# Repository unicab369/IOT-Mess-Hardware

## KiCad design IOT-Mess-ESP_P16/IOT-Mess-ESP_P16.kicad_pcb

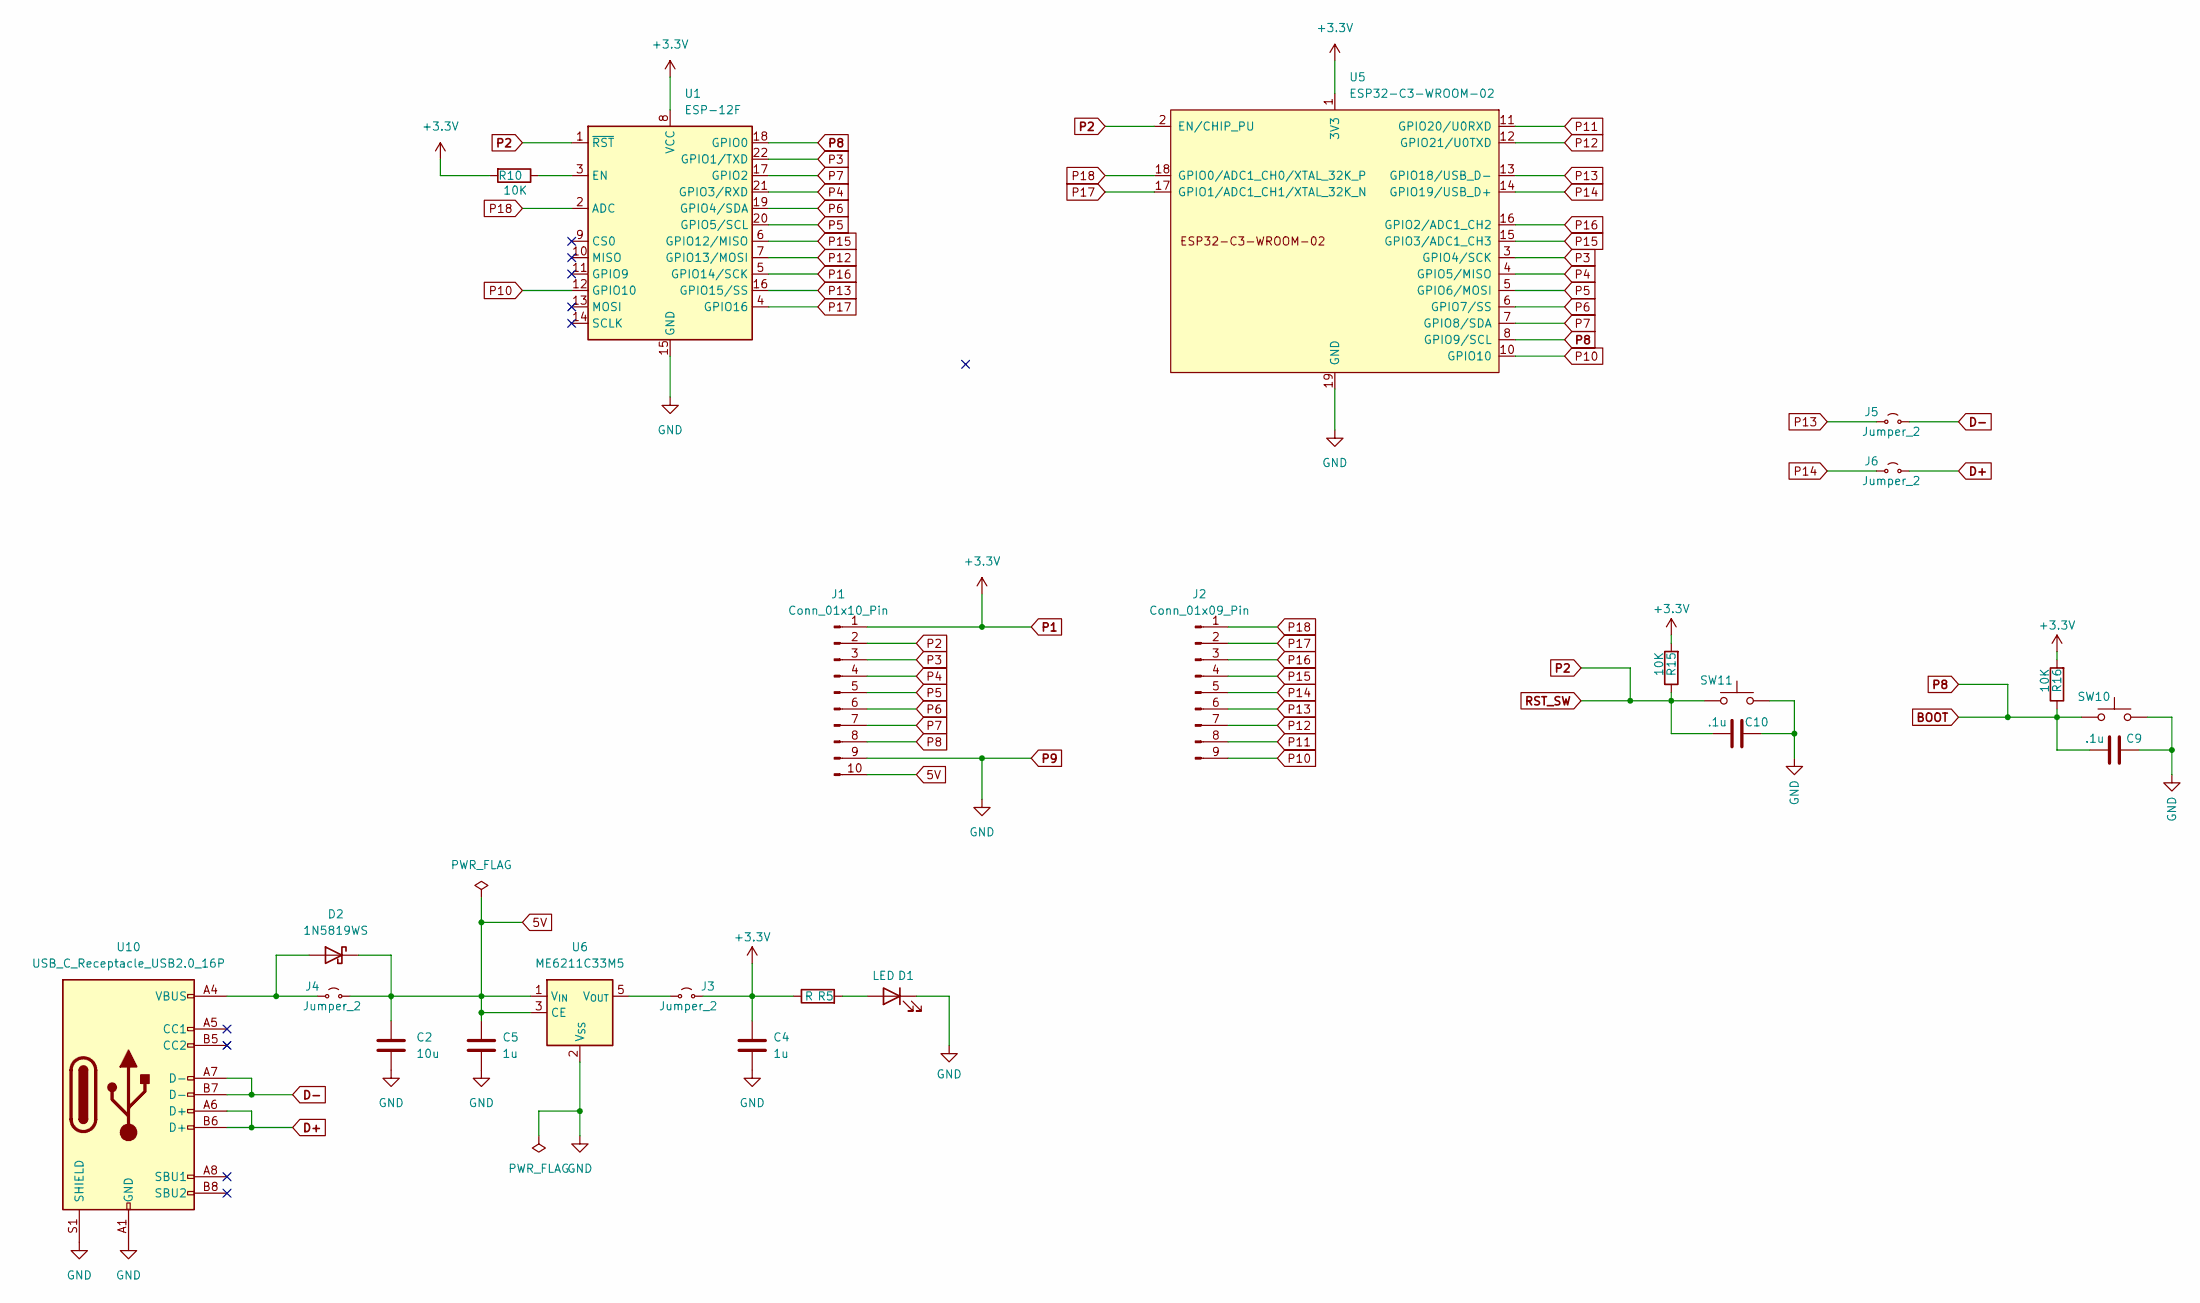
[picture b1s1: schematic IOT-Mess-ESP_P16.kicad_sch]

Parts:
C2: 10u; C_0603_1608Metric
C4, C5: 1u; C_0603_1608Metric
C9, C10: .1u; C_0603_1608Metric
D1: LED; LED_0603_1608Metric
D2: 1N5819WS; D_SOD-323
J1: Conn_01x10_Pin; PinHeader_1x10_P2.54mm_Vertical
J2: Conn_01x09_Pin; PinHeader_1x09_P2.54mm_Vertical
J3, J4, J5, J6: Jumper_2; Jumpper-triangle
R5: R; R_0603_1608Metric
R10, R15, R16: 10K; R_0603_1608Metric
SW10, SW11: SW_Push; SW_SPST_PTS810
U1: ESP-12F; ESP-12E
U5: ESP32-C3-WROOM-02
U6: ME6211C33M5; SOT-23-5
U10: USB_C_Receptacle_USB2.0_16P; USB_C_Receptacle_HRO_TYPE-C-31-M-12

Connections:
5V: C2.1, C5.1, D2.1 (K), J1.10, J4.2 (B), U6.1 (V_{IN}), U6.3 (CE)
BOOT: C9.1, J1.8, R16.1, SW10.1, U1.18 (GPIO0), U5.8 (GPIO9/SCL)
D+: J6.2 (B), U10.A6 (D+), U10.B6 (D+)
D-: J5.2 (B), U10.A7 (D-), U10.B7 (D-)
unnamed: D1.2 (A), R5.2
unnamed: D2.2 (A), J4.1 (A), U10.A4 (VBUS), U10.A9 (VBUS), U10.B4 (VBUS), U10.B9 (VBUS)
unnamed: J3.2 (B), U6.5 (V_{OUT})
unnamed: R10.1, U1.3 (EN)
P1: C4.1, J1.1, J3.1 (A), R5.1, R10.2, R15.2, R16.2, U1.8 (VCC), U5.1 (3V3)
P2: C10.1, J1.2, R15.1, SW11.1, U1.1 (~RST), U5.2 (EN/CHIP_PU)
P3: J1.3, U1.22 (GPIO1/TXD), U5.3 (GPIO4/SCK)
P4: J1.4, U1.21 (GPIO3/RXD), U5.4 (GPIO5/MISO)
P5: J1.5, U1.20 (GPIO5/SCL), U5.5 (GPIO6/MOSI)
P6: J1.6, U1.19 (GPIO4/SDA), U5.6 (GPIO7/SS)
P7: J1.7, U1.17 (GPIO2), U5.7 (GPIO8/SDA)
P9: C2.2, C4.2, C5.2, C9.2, C10.2, D1.1 (K), J1.9, SW10.2, SW11.2, U1.15 (GND), U5.9 (GND), U5.19 (GND), U6.2 (V_{SS}), U10.A1 (GND), U10.A12 (GND), U10.B1 (GND), U10.B12 (GND), U10.S1 (SHIELD)
P10: J2.9, U1.12 (GPIO10), U5.10 (GPIO10)
P11: J2.8, U5.11 (GPIO20/U0RXD)
P12: J2.7, U1.7 (GPIO13/MOSI), U5.12 (GPIO21/U0TXD)
P13: J2.6, J5.1 (A), U1.16 (GPIO15/SS), U5.13 (GPIO18/USB_D-)
P14: J2.5, J6.1 (A), U5.14 (GPIO19/USB_D+)
P15: J2.4, U1.6 (GPIO12/MISO), U5.15 (GPIO3/ADC1_CH3)
P16: J2.3, U1.5 (GPIO14/SCK), U5.16 (GPIO2/ADC1_CH2)
P17: J2.2, U1.4 (GPIO16), U5.17 (GPIO1/ADC1_CH1/XTAL_32K_N)
P18: J2.1, U1.2 (ADC), U5.18 (GPIO0/ADC1_CH0/XTAL_32K_P)

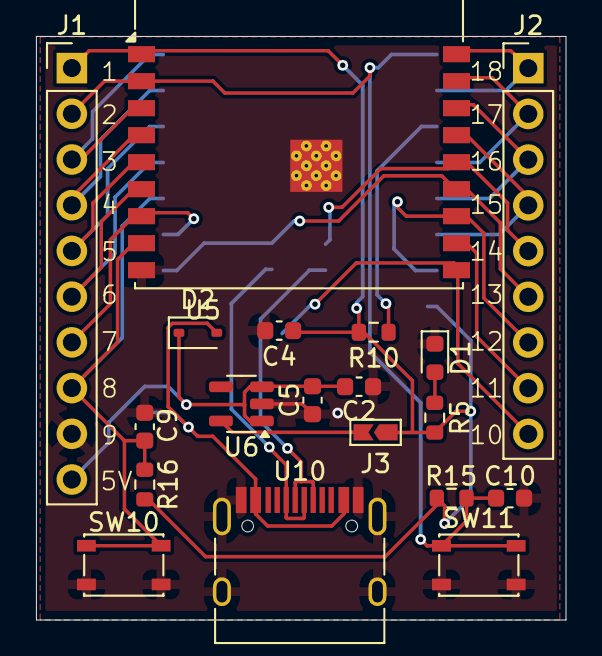
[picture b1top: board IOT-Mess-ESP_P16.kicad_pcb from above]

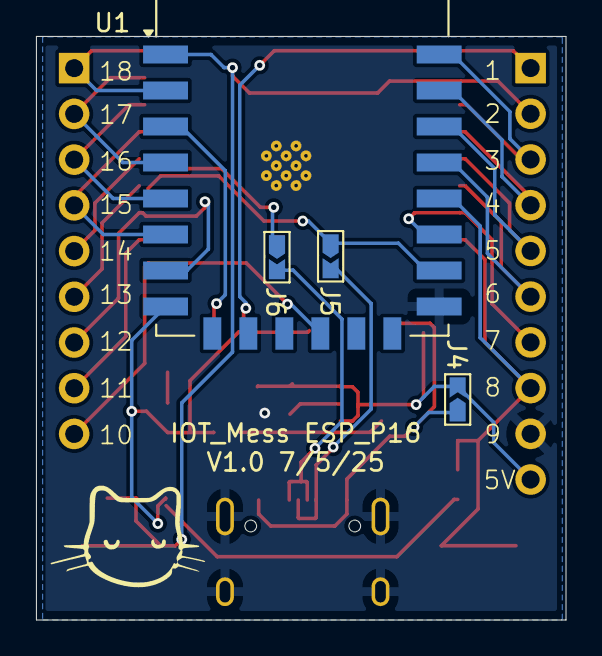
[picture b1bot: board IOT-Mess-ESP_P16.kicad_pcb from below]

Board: 2 copper layers, 29.4 x 32.4 mm, 23 parts (4 on the bottom side), 25 nets.

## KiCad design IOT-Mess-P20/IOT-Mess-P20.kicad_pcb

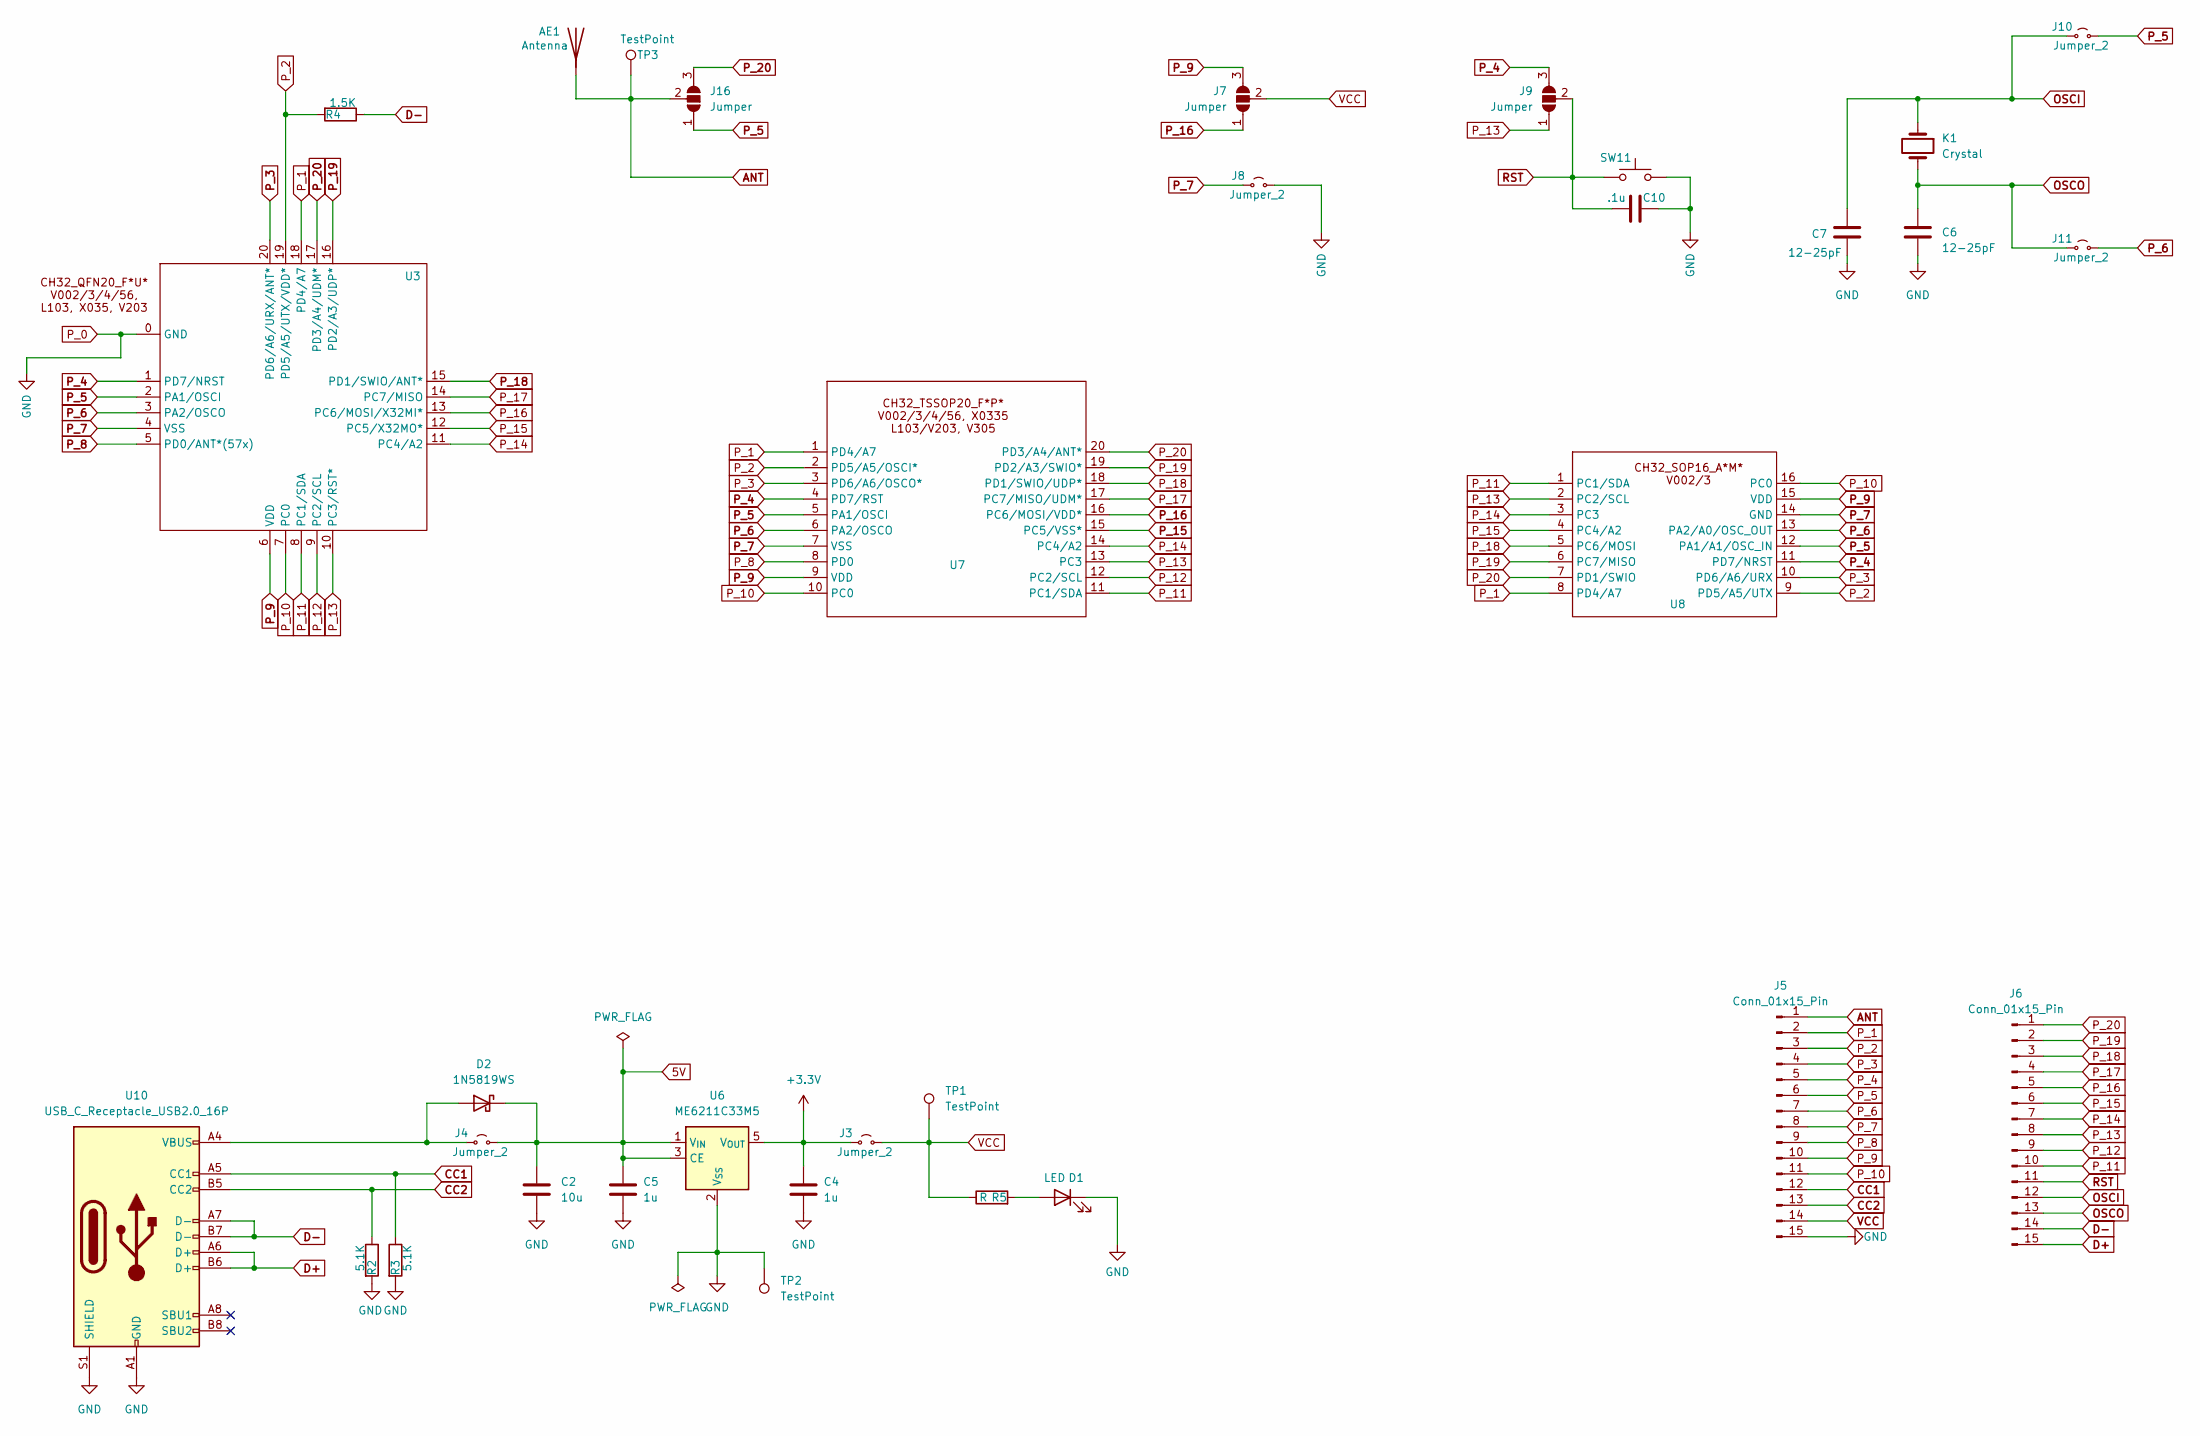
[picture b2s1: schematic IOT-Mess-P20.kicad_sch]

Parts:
AE1: Antenna; Texas_SWRA117D_2.4GHz_Right
C2: 10u; C_0603_1608Metric
C4, C5: 1u; C_0603_1608Metric
C6, C7: 12-25pF; C_0603_1608Metric
C10: .1u; C_0603_1608Metric
D1: LED; LED_0603_1608Metric
D2: 1N5819WS; D_SOD-323
J3, J4, J8, J10, J11: Jumper_2; Jumpper-triangle
J5, J6: Conn_01x15_Pin; PinHeader_1x15_P2.54mm_Vertical
J7, J9, J16: Jumper; Jumper-3_P1.3mm_Open_RoundedPad1.0x1.5mm
K1: Crystal; Crystal_SMD_3225-4Pin_3.2x2.5mm
R2, R3: 5.1K; R_0603_1608Metric
R4: 1.5K; R_0603_1608Metric
R5: R; R_0603_1608Metric
SW11: SW_Push; SW_SPST_PTS810
TP1, TP2, TP3: TestPoint
U3: QFN-20-1EP_3x3mm_P0.4mm_EP1.65x1.65mm_ThermalVias
U6: ME6211C33M5; SOT-23-5
U7: TSSOP-20_4.4x6.5mm_P0.65mm
U8: SOP-16_3.9x9.9mm_P1.27mm
U10: USB_C_Receptacle_USB2.0_16P; USB_C_Receptacle_HRO_TYPE-C-31-M-12

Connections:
5V: C2.1, C5.1, D2.1 (K), J4.2 (B), U6.1 (V_{IN}), U6.3 (CE)
+3.3V: C4.1, J3.1 (A), U6.5 (V_{OUT})
ANT: AE1.1 (A), J5.1, J16.2 (C), TP3.1
CC1: J5.12, R3.1, U10.A5 (CC1)
CC2: J5.13, R2.1, U10.B5 (CC2)
D+: J6.15, U10.A6 (D+), U10.B6 (D+)
D-: J6.14, R4.1, U10.A7 (D-), U10.B7 (D-)
unnamed: D1.2 (A), R5.2
unnamed: D2.2 (A), J4.1 (A), U10.A4 (VBUS), U10.A9 (VBUS), U10.B4 (VBUS), U10.B9 (VBUS)
OSCI: C7.1, J6.12, J10.1 (A), K1.1
OSCO: C6.1, J6.13, J11.1 (A), K1.2
P_0: C2.2, C4.2, C5.2, C6.2, C7.2, C10.2, D1.1 (K), J5.15, J8.2 (B), R2.2, R3.2, SW11.2, TP2.1, U3.0 (GND), U6.2 (V_{SS}), U10.A1 (GND), U10.A12 (GND), U10.B1 (GND), U10.B12 (GND), U10.S1 (SHIELD)
P_1: J5.2, U3.18 (PD4/A7), U7.1 (PD4/A7), U8.8 (PD4/A7)
P_2: J5.3, R4.2, U3.19 (PD5/A5/UTX/VDD*), U7.2 (PD5/A5/OSCI*), U8.9 (PD5/A5/UTX)
P_3: J5.4, U3.20 (PD6/A6/URX/ANT*), U7.3 (PD6/A6/OSCO*), U8.10 (PD6/A6/URX)
P_4: J5.5, J9.3 (B), U3.1 (PD7/NRST), U7.4 (PD7/RST), U8.11 (PD7/NRST)
P_5: J5.6, J10.2 (B), J16.1 (A), U3.2 (PA1/OSCI), U7.5 (PA1/OSCI), U8.12 (PA1/A1/OSC_IN)
P_6: J5.7, J11.2 (B), U3.3 (PA2/OSCO), U7.6 (PA2/OSCO), U8.13 (PA2/A0/OSC_OUT)
P_7: J5.8, J8.1 (A), U3.4 (VSS), U7.7 (VSS), U8.14 (GND)
P_8: J5.9, U3.5 (PD0/ANT*(57x)), U7.8 (PD0)
P_9: J5.10, J7.3 (B), U3.6 (VDD), U7.9 (VDD), U8.15 (VDD)
P_10: J5.11, U3.7 (PC0), U7.10 (PC0), U8.16 (PC0)
P_11: J6.10, U3.8 (PC1/SDA), U7.11 (PC1/SDA), U8.1 (PC1/SDA)
P_12: J6.9, U3.9 (PC2/SCL), U7.12 (PC2/SCL)
P_13: J6.8, J9.1 (A), U3.10 (PC3/RST*), U7.13 (PC3), U8.2 (PC2/SCL)
P_14: J6.7, U3.11 (PC4/A2), U7.14 (PC4/A2), U8.3 (PC3)
P_15: J6.6, U3.12 (PC5/X32MO*), U7.15 (PC5/VSS*), U8.4 (PC4/A2)
P_16: J6.5, J7.1 (A), U3.13 (PC6/MOSI/X32MI*), U7.16 (PC6/MOSI/VDD*)
P_17: J6.4, U3.14 (PC7/MISO), U7.17 (PC7/MISO/UDM*)
P_18: J6.3, U3.15 (PD1/SWIO/ANT*), U7.18 (PD1/SWIO/UDP*), U8.5 (PC6/MOSI)
P_19: J6.2, U3.16 (PD2/A3/UDP*), U7.19 (PD2/A3/SWIO*), U8.6 (PC7/MISO)
P_20: J6.1, J16.3 (B), U3.17 (PD3/A4/UDM*), U7.20 (PD3/A4/ANT*), U8.7 (PD1/SWIO)
RST: C10.1, J6.11, J9.2 (C), SW11.1
VCC: J3.2 (B), J5.14, J7.2 (C), R5.1, TP1.1

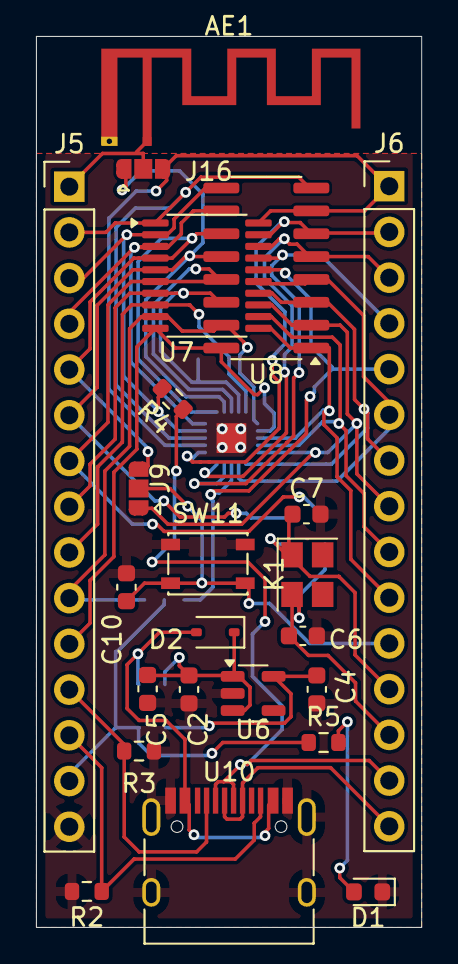
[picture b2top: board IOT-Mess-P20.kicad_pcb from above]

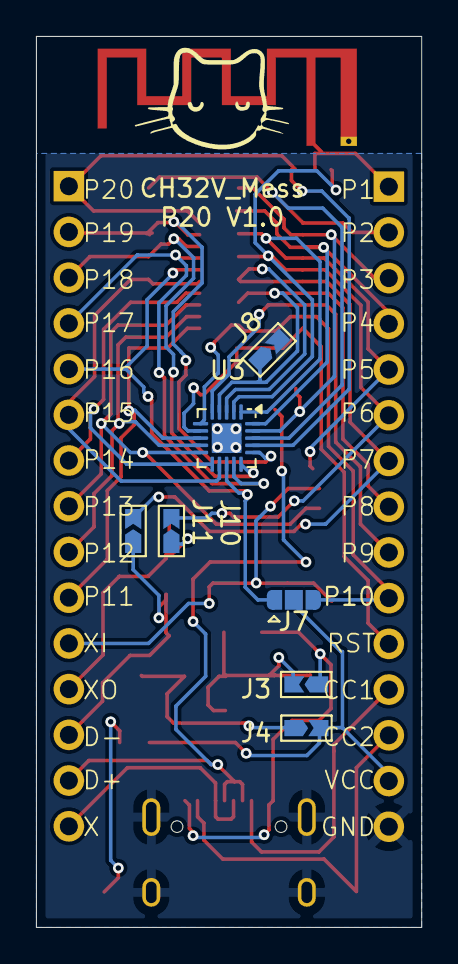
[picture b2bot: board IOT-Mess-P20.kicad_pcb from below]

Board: 2 copper layers, 21.4 x 49.5 mm, 30 parts (7 on the bottom side), 34 nets.

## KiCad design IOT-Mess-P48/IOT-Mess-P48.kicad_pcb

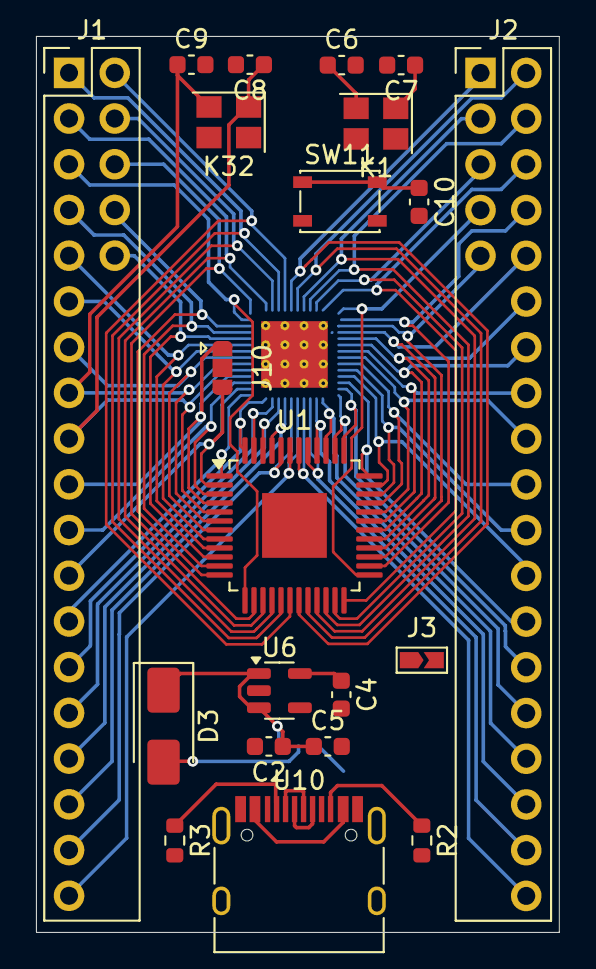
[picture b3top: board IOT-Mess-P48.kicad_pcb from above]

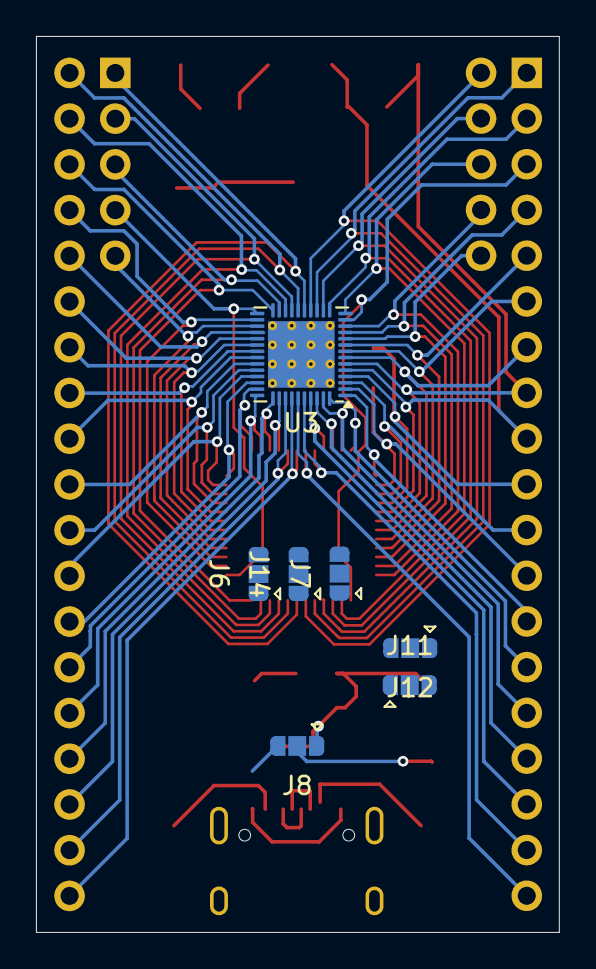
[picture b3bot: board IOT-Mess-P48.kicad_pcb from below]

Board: 2 copper layers, 29.1 x 49.8 mm, 28 parts (7 on the bottom side), 59 nets.

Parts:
C2: 10u; C_0603_1608Metric
C4, C5: 1u; C_0603_1608Metric
C6, C7: 12-25pF; C_0603_1608Metric
C8, C9: 15-30pF; C_0603_1608Metric
C10: .1u; C_0603_1608Metric
D3: SS14; D_SMA
J1, J2: Conn_02x19_Odd_Even; PinHeader_2x19_P2.54mm_Vertical
J3: Jumper_2; Jumpper-triangle
J6, J7, J8, J10, J11, J12, J14: Jumper; Jumper-3_P1.3mm_Open_RoundedPad1.0x1.5mm
K1, K32: Crystal; Crystal_SMD_3225-4Pin_3.2x2.5mm
R2, R3: 5.1K; R_0603_1608Metric
SW11: SW_Push; SW_SPST_PTS810
U1: LQFP-48-1EP_7x7mm_P0.5mm_EP3.6x3.6mm
U3: CH32L103C8T6; QFN-48-1EP_5x5mm_P0.35mm_EP3.7x3.7mm_ThermalVias
U6: ME6211C33M5; SOT-23-5
U10: USB_C_Receptacle_USB2.0_16P; USB_C_Receptacle_HRO_TYPE-C-31-M-12

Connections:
5V: C2.1, C5.1, D3.1 (K), J8.1 (A), U6.1 (V_{IN}), U6.3 (CE)
+3.3V: C4.1, J3.1 (A), U6.5 (V_{OUT})
D+: U10.A6 (D+), U10.B6 (D+)
D-: U10.A7 (D-), U10.B7 (D-)
GND: C2.2, C4.2, C5.2, C6.2, C7.2, C8.2, C9.2, C10.2, J11.2 (C), J12.2 (C), R2.2, R3.2, SW11.2, U1.49 (VSS), U3.49 (VSS), U6.2 (V_{SS}), U10.A1 (GND), U10.A12 (GND), U10.B1 (GND), U10.B12 (GND), U10.S1 (SHIELD)
unnamed: D3.2 (A), J8.2 (C)
unnamed: J8.3 (B), U10.A4 (VBUS), U10.A9 (VBUS), U10.B4 (VBUS), U10.B9 (VBUS)
unnamed: C7.1, J10.2 (C), K1.1
unnamed: R3.1, U10.A5 (CC1)
unnamed: R2.1, U10.B5 (CC2)
P_1: J1.25, J7.3 (B), U1.1 (VBAT), U3.1 (VBAT)
P_2: J1.23, J10.3 (B), U1.2 (PC13), U3.2 (PC13)
P_3: C6.1, J1.21, K1.2, U1.3 (PC14/OSC32_IN), U3.3 (PC14/OSC32_IN)
P_4: J1.19, J10.1 (A), U1.4 (PC15/OSC32_OUT), U3.4 (PC15/OSC32_OUT)
P_5: C8.1, J1.17, K32.1, U1.5 (PD0/OSC_IN), U3.5 (PD0/OSC_IN)
P_6: C9.1, J1.15, K32.2, U1.6 (PD1/OSC_OUT), U3.6 (PD1/OSC_OUT)
P_7: C10.1, J1.13, SW11.1, U1.7 (NRST), U3.7 (NRST)
P_8: J1.11, J11.3 (B), U1.8 (VSSA), U3.8 (VSSA)
P_9: J1.9, J7.1 (A), U1.9 (VDDA), U3.9 (VDDA)
P_10: J1.10, U1.10 (PA0/ADC0/WKUP), U3.10 (PA0/ADC0/WKUP)
P_11: J1.7, U1.11 (PA1/ADC1), U3.11 (PA1/ADC1)
P_12: J1.8, U1.12 (PA2/ADC2), U3.12 (PA2/ADC2)
P_13: J1.5, U1.13 (PA3/ADC3), U3.13 (PA3/ADC3)
P_14: J1.6, U1.14 (PA4/ADC), U3.14 (PA4/ADC4/ADC0)
P_15: J1.3, U1.15 (PA5/ADC5), U3.15 (PA5/ADC5/ADC1)
P_16: J1.4, U1.16 (PA6/ADC6), U3.16 (PA6/ADC6)
P_17: J1.1, U1.17 (PA7/ADC7), U3.17 (PA7/ADC7)
P_18: J1.2, U1.18 (PB0/ADC8), U3.18 (PB0/ADC8)
P_19: J2.1, U1.19 (PB1/ADC9), U3.19 (PB1/ADC9)
P_20: J2.2, U1.20 (PB2/BOTT), U3.20 (PB2/BOOT)
P_21: J2.3, U1.21 (PB10), U3.21 (PB10)
P_22: J2.4, U1.22 (PB11), U3.22 (BP11)
P_23: J2.5, J11.1 (A), U1.23 (VSS_1), U3.23 (VSS_1)
P_24: J2.6, J6.3 (B), U1.24 (VDD_VIO_1), U3.24 (VDD_1)
P_25: J2.7, U1.25 (PB12), U3.25 (PD12)
P_26: J2.8, U1.26 (PB13), U3.26 (PD13)
P_27: J2.9, U1.27 (PB14), U3.27 (PD14)
P_28: J2.10, U1.28 (PB15), U3.28 (PD15)
P_29: J2.12, U1.29 (PA8), U3.29 (PA8)
P_30: J2.14, U1.30 (PA9), U3.30 (PA9)
P_31: J2.16, U1.31 (PA10), U3.31 (PA10)
P_32: J2.18, U1.32 (PA11/USB1_DM), U3.32 (PA11/USB_HDM)
P_33: J2.20, J14.1 (A), U1.33 (PA12/USB1_DP), U3.33 (PA12/USB_HDP)
P_34: J2.22, U1.34 (AP13/SWDIO), U3.34 (PA23/SWDIO)
P_35: J2.24, J12.3 (B), U1.35 (VSS_2), U3.35 (VSS_2)
P_36: J2.26, J6.1 (A), U1.36 (VDD_2), U3.36 (VDD_2)
P_37: J2.28, U1.37 (PA14/SWCLK), U3.37 (PA14/SWCLK)
P_38: J2.30, U1.38 (PA15), U3.38 (PA15)
P_39: J2.32, U1.39 (PB3), U3.39 (PB3)
P_40: J2.34, U1.40 (PB4), U3.40 (PB4)
P_41: J2.36, U1.41 (PB5), U3.41 (PB5)
P_42: J2.38, U1.42 (PB6/USB2_DM), U3.42 (PB6/USB2_DM)
P_43: J1.37, U1.43 (PB7/USB2_DP), U3.43 (PB7/USB2_DP)
P_44: J1.35, U1.44 (BOOT0), U3.44 (BOOT0)
P_45: J1.33, U1.45 (PB8), U3.45 (PB8)
P_46: J1.31, U1.46 (PB9), U3.46 (PB9)
P_47: J1.29, J12.1 (A), U1.47 (VSS_3), U3.47 (VSS_3)
P_48: J1.27, J14.3 (B), U1.48 (VDD_VIO_3), U3.48 (VDD_3)
VCC: J3.2 (B), J6.2 (C), J7.2 (C), J14.2 (C)

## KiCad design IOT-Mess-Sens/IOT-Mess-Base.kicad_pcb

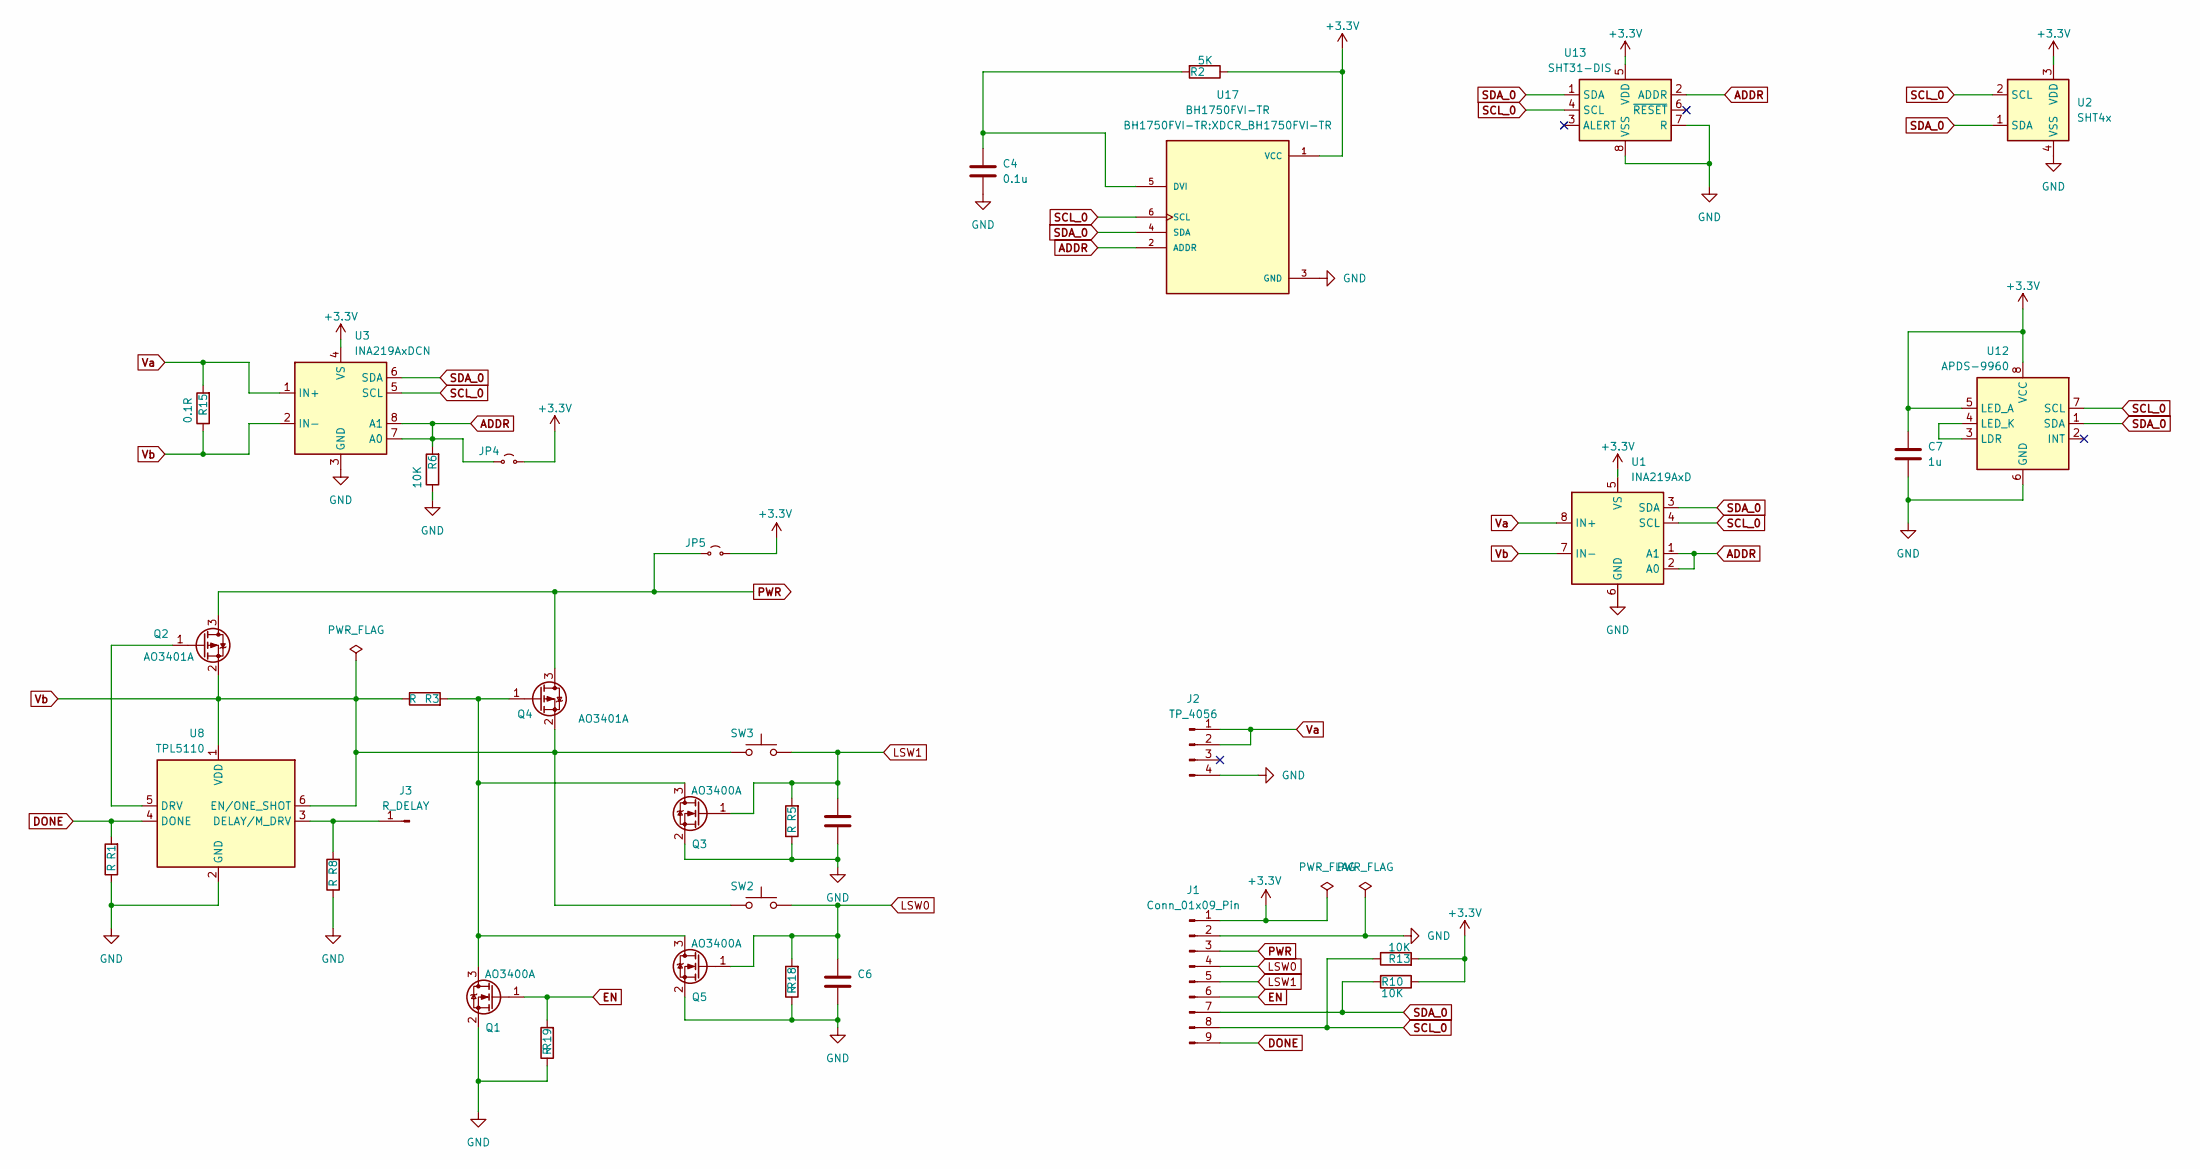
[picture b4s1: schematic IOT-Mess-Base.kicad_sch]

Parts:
C4: 0.1u; C_0603_1608Metric
C5, C6: C; C_0603_1608Metric
C7: 1u; C_0603_1608Metric
J1: Conn_01x09_Pin; PinHeader_1x09_P2.54mm_Vertical
J2: TP_4056; TP_Charger
J3: R_DELAY; PinHeader_1x01_P1.00mm_Vertical
JP4, JP5: Jp_2; SolderJumper-2_P1.3mm_Open_Pad1.0x1.5mm
Q1, Q3, Q5: AO3400A; SOT-23
Q2, Q4: AO3401A; SOT-23
R1, R3, R5, R8, R18, R19: R; R_0603_1608Metric
R2: 5K; R_0603_1608Metric
R6, R10, R13: 10K; R_0603_1608Metric
R15: 0.1R; R_2512_6332Metric
SW2, SW3: SW_Push; SW_SPST_PTS810
U1: INA219AxD; SOIC-8_3.9x4.9mm_P1.27mm
U2: SHT4x; Sensirion_DFN-4_1.5x1.5mm_P0.8mm_SHT4x_NoCentralPad
U3: INA219AxDCN; SOT-23-8
U8: TPL5110; SOT-23-6
U12: APDS-9960; Avago_APDS-9960
U13: SHT31-DIS; Sensirion_DFN-8-1EP_2.5x2.5mm_P0.5mm_EP1.1x1.7mm
U17: BH1750FVI-TR; XDCR_BH1750FVI-TR; PARTREV D

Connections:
+3.3V: C7.1, J1.1, JP4.2 (B), JP5.2 (B), R2.1, R10.1, R13.2, U1.5 (VS), U2.3 (VDD), U3.4 (VS), U12.5 (LED_A), U12.8 (VCC), U13.5 (VDD), U17.1 (VCC)
ADDR: JP4.1 (A), R6.2, U1.1 (A1), U1.2 (A0), U3.7 (A0), U3.8 (A1), U13.2 (ADDR), U17.2 (ADDR)
DONE: J1.9, R1.2, U8.4 (DONE)
EN: J1.6, Q1.1 (G), R19.2
GND: C4.2, C5.2, C6.2, C7.2, J1.2, J2.4, Q1.2 (S), Q3.2 (S), Q5.2 (S), R1.1, R5.1, R6.1, R8.1, R18.1, R19.1, U1.6 (GND), U2.4 (VSS), U3.3 (GND), U8.2 (GND), U12.6 (GND), U13.7 (R), U13.8 (VSS), U13.9 (VSS), U17.3 (GND)
LSW0: C6.1, J1.4, Q5.1 (G), R18.2, SW2.2
LSW1: C5.1, J1.5, Q3.1 (G), R5.2, SW3.2
unnamed: J3.1, R8.2, U8.3 (DELAY/M_DRV)
unnamed: Q1.3 (D), Q3.3 (D), Q4.1 (G), Q5.3 (D), R3.2
unnamed: Q2.1 (G), U8.5 (DRV)
unnamed: U12.3 (LDR), U12.4 (LED_K)
unnamed: C4.1, R2.2, U17.5 (DVI)
PWR: J1.3, JP5.1 (A), Q2.3 (D), Q4.3 (D)
SCL_0: J1.8, R13.1, U1.4 (SCL), U2.2 (SCL), U3.5 (SCL), U12.7 (SCL), U13.4 (SCL), U17.6 (SCL)
SDA_0: J1.7, R10.2, U1.3 (SDA), U2.1 (SDA), U3.6 (SDA), U12.1 (SDA), U13.1 (SDA), U17.4 (SDA)
Va: J2.1, J2.2, R15.2, U1.8 (IN+), U3.1 (IN+)
Vb: Q2.2 (S), Q4.2 (S), R3.1, R15.1, SW2.1, SW3.1, U1.7 (IN-), U3.2 (IN-), U8.1 (VDD), U8.6 (EN/ONE_SHOT)

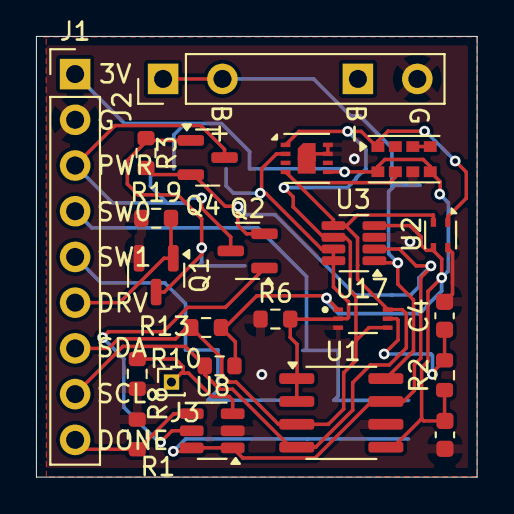
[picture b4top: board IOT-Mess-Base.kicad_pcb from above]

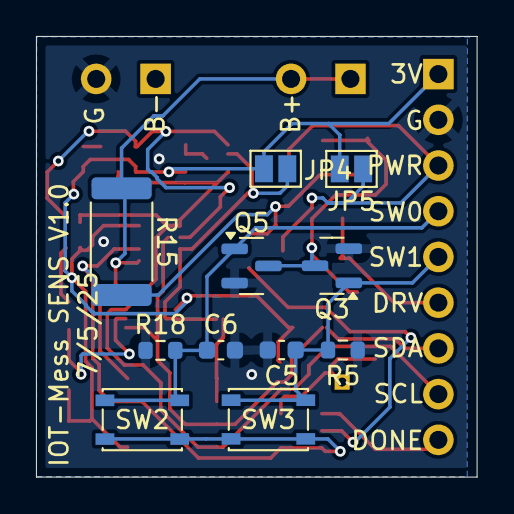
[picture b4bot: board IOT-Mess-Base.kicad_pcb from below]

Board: 2 copper layers, 24.5 x 24.5 mm, 34 parts (11 on the bottom side), 17 nets.
